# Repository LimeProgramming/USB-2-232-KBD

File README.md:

# USB-2-232-KBD
 Converts USB mice and USB keyboards to serial mice and XT-AT-PS/2 keyboards.

# Development
In progress, not ready for production

## About
This project is an extension of a previous project that you can find here  [previous project that you can find here.](https://github.com/LimeProgramming/USB-serial-mouse-adapter)
My previous project just converted USB mice to Serial mice, this project aims to also convert USB keyboards to XT-AT-PS/2 keyboards. 

# Features
### KVM:
Support for use on KVMs has been added as of version 1.1.1. 
It works fine on my **one**, startech branded, KVM that I have test with. Given that TinyUSB is a bit picky, your results may vary.

## Mouse Features
With this adapter you can convert a modern native USB mouse to a classic serial mouse. 
Want to use an optical mouse on a 386 running Wolfenstein 3D? Well now you can! Want to use a wireless optical mouse on a 486 running Doom? Well you might be able to! (depending on the mouse)

**Supported Protocols:**
- Microsoft Two Button
- Logitech Three Button
- Microsoft Wheel

## Hardware

For the PCB I tried to mimic real keyboard hardware where possible. My old AT keyboard uses 2.2k pull-ups, ferrites, clamp caps and so this PCB does as well for the keyboard interface. Interfacing directly with the GPIO via level shifters uses much higher pullup values, no clamp caps to mitigate signal bounce, no ferrites to mitigate signal noise and importantly, no fuse on the power in line from the host PC. Technically, using a level shifters should work just fine but it is a bit out of spec so early AT and XT machines *may* have issues with level shifters.

I mentioned a fuse, there is a 750ma poly fuse on the PCB as standard. It seems that most AT motherboards have a 1 amp fuse for their keyboard, however that will need to be changed if it pops. While RGB keyboards and mice use more power than the old AT keyboards, there is still more than enough headroom for powering them. Issues can pop up if you're pulling too much power from the keyboard port or back feeding power into the motherboard. For example, my KVM will pull power from the USB port if it is not being powered by it's power adapter, it could potentially pull more than 1 amp, so hopefully the self resetting poly fuse will pop before the 1amp fuse on your motherboard. 

If you want to power the adapter from the keyboard port, put a jumper on pin header J5, label KBDPWR. 
**Important:** If you're powering the adapter using any other methods (eg, built in mini USB, picos micro usb, J4 pin header or a KVM) you must take the jumper off of J5. You risk back feeding a connected computer. 

### Din or PS/2 Port
The PCB can use either a din or a PS/2 port in the same footprint. You can choose which you want to use based on your use case. Recommended use case would be to use the PS/2 port because 6 pin mini din cables are cheap and easy to find.

### Resetting the adapter
Forgot your settings and can't get the adapter working? Don't worry.
There are three different ways to reset the adapter:

#### --- Serial Terminal
As written above, you can reset the adapter back to default settings from the terminal. You can connect to the unused UART of the pico regardless of the settings of the mouse. 

#### --- Small Flat Head Screwdriver

**How To:**
1. Press a small flat head into the position shown above.
2. Power on the adapter and the Picos built-in LED will glow solid.
3. Hold the flat head in position for two or three seconds for the Picos LED to start blinking.
4. Once it is blinking, you can let go of the GPIO and press the reset button.
5. The adapter will boot up with default settings.
#### --- Nuke UF2
**How To:**
1. Download the [flash_nuke.uf2](https://datasheets.raspberrypi.com/soft/flash_nuke.uf2) file.
2. Connect the adapter to your PC using the microusb port built into the Pi Pico.
3. Hold Reset, then bootsel, then release reset then bootsel. This will make the Pico appear as a removable storage device. 
4. Drag the flash_nuke.uf2 file to the storage device. This will reset the flash the on the Pi Pico.
5. The Pico should reboot on its own and show up as a removable storage device again. If it doesn't, tap the reset button.
6. Download the latest firmware and drag that UF2 file to the storage device.
7. The adapter will boot up with default settings.

# Compiling the Firmware
The default mouse settings can be edited in `default_config.h` prior to compilation. You can use this to set the default settings for your own configuration. 

The build environment is a normal PicoSDK setup, there are several guides out the for both Linux and Windows.  From experience the setup is easier in Linux. 

You'll need the following Libs:
 - [**PicoSDK Version: 1.4.0**](https://github.com/raspberrypi/pico-sdk)
 - [**TinyUSB Version: 0.14.0**](https://github.com/hathach/tinyusb)
 - [**TUSB Xinput**](https://github.com/Ryzee119/tusb_xinput)

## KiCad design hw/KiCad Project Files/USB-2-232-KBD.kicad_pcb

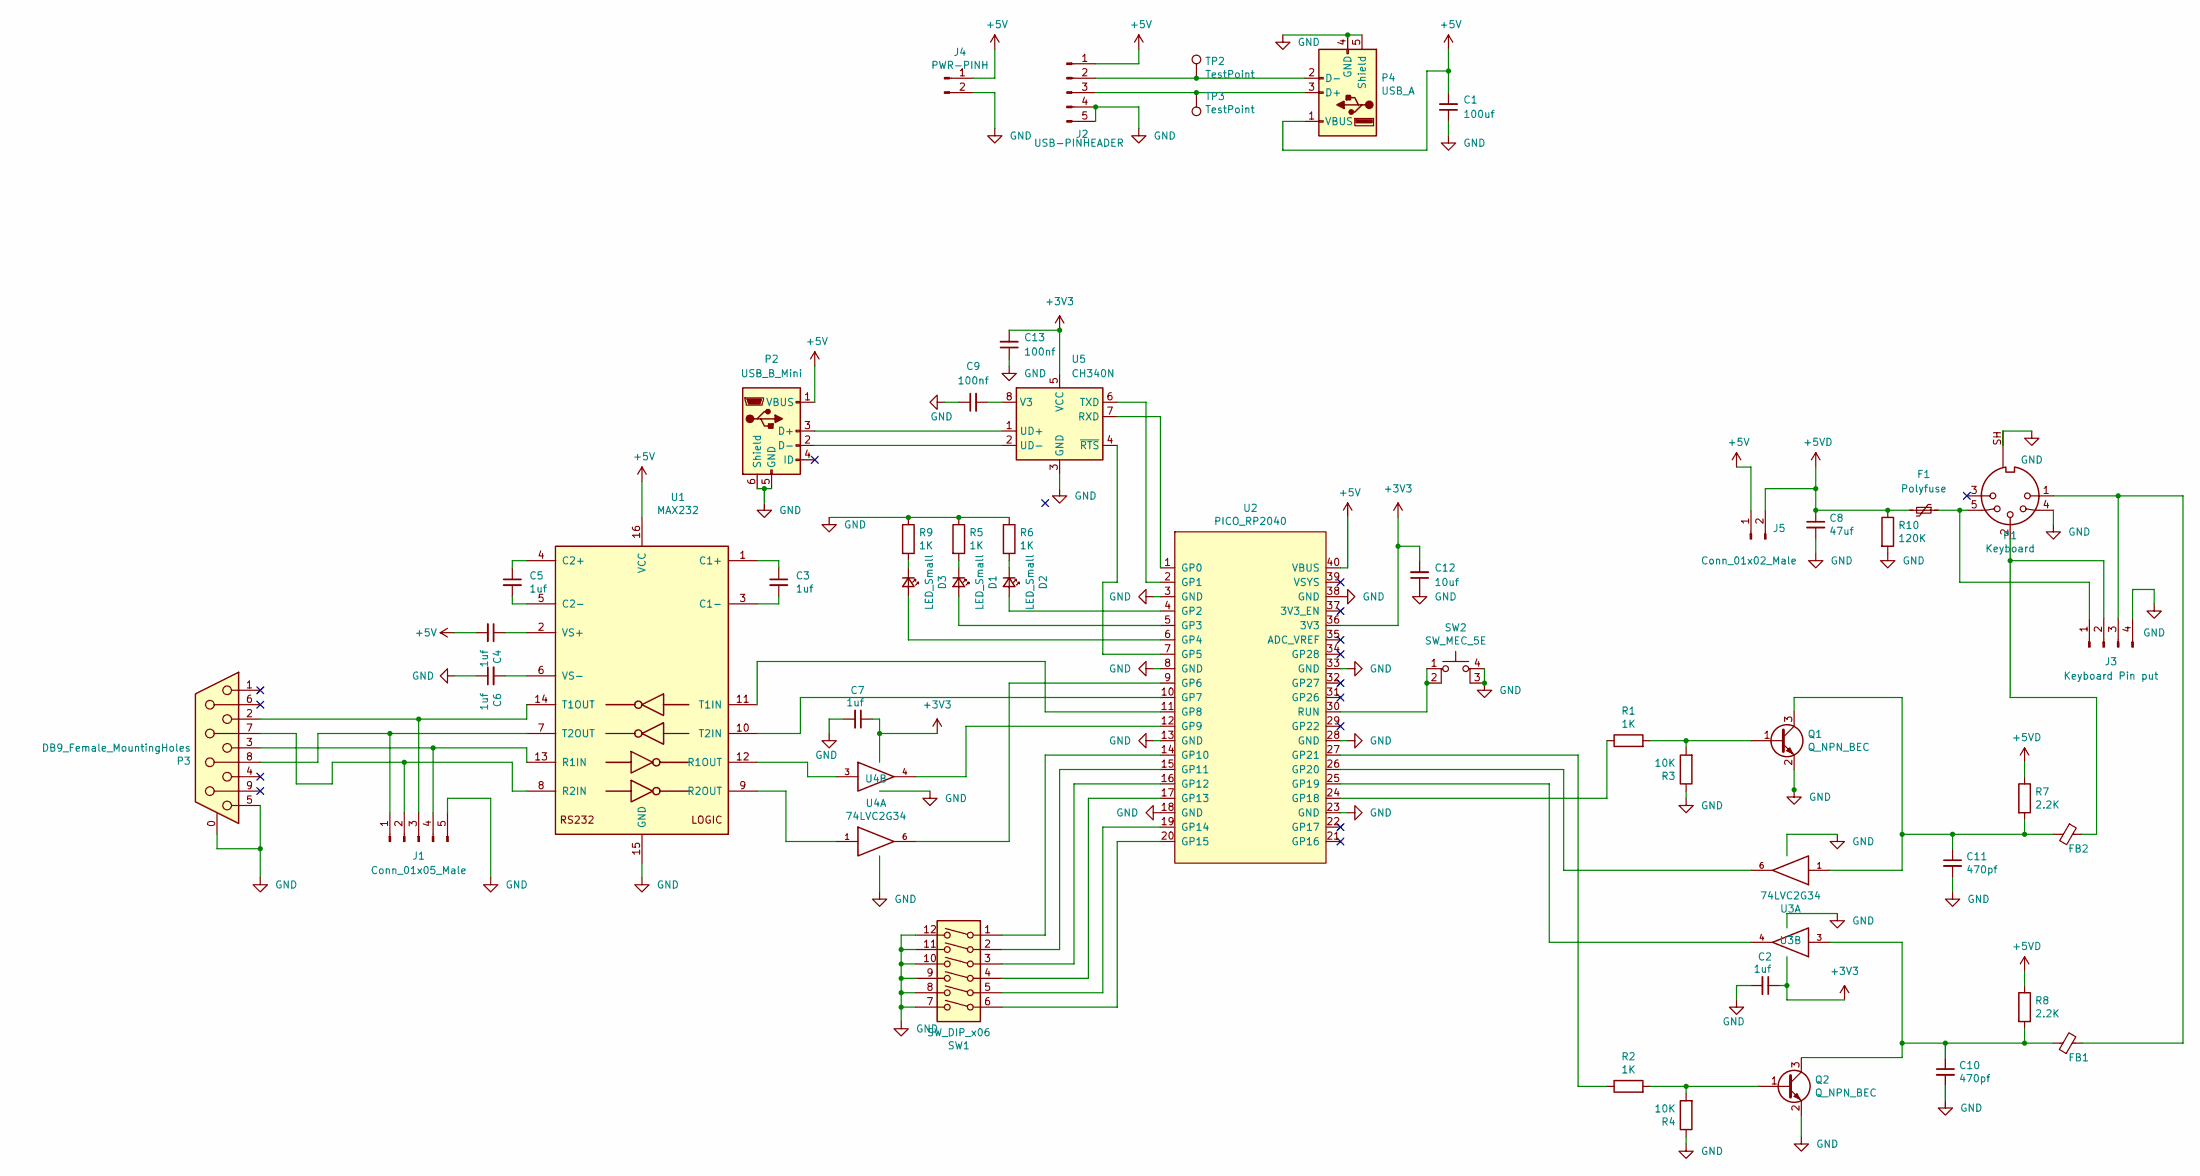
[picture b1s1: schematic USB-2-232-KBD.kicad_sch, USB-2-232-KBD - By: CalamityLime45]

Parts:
C1: 100uf; C_1206_3216Metric; JLC part C15008
C2, C4, C5, C7: 1uf; C_0402_1005Metric; JLC part C52923
C3, C6: 1uf; C_0402_1005Metric_ref-flip; JLC part C52923
C8: 47uf; C_0805_2012Metric; JLC part C16780
C9: 100nf; C_0402_1005Metric; JLC part C1525
C10: 470pf; C_0402_1005Metric
C11: 470pf; C_0402_1005Metric; JLC part C1537
C12: 10uf; C_1206_3216Metric; JLC part C13585
C13: 100nf; C_0402_1005Metric
D1: LED_Small; LED_0805_MOUSE; JLC part C2296
D2: LED_Small; LED_0805_PWR; JLC part C84256
D3: LED_Small; LED_0805_KB; JLC part C2296
F1: Polyfuse; PolyFuse_1206; JLC part C883129
FB1: Ferrite; FB_0805_2012Metric; JLC part C1015
FB2: Ferrite; FB_0805_2012Metric; JLC Part C1015
J1: Conn_01x05_Male; PinHeader_ALT_SERIAL_OUT_V2
J2: USB-PINHEADER; PinHeader_ALT_USB_IN
J3: Keyboard Pin put; AT_Keyboard_pin
J4: PWR-PINH; PinHeader_ALT_PWR_IN
J5: Conn_01x02_Male; PinHeader_PWR_FROM_AT
P1: Keyboard; DIN-PS2-COMBO
P2: USB_B_Mini; USB_Mini-B; JLC part C2977777
P3: DB9_Female_MountingHoles; DSUB-9_Female_Horizontal_P2.77x2.84mm_EdgePinOffset7.70mm_H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
P4: USB_A; USB_A_Wuerth_614004134726_Horizontal
Q1, Q2: Q_NPN_BEC; SOT-23-3; JLC part C8512
R1, R2, R5, R6, R9: 1K; R_0402_LEDS; JLC part C11702
R3, R4: 10K; R_0402_LEDS; JLC part C25744
R7, R8: 2.2K; R_0805_2012Metric; JLC part C17520
R10: 120K; R_0805_2012Metric; JLC Part C17436
SW1: SW_DIP_x06; SW_DIP_SPSTx06_Slide_9.78x17.42mm_W7.62mm_P2.54mm
SW2: SW_MEC_5E; SW_PUSH_6mm
TP2: TestPoint; TP2_Pad_TH_1.5x1.5
TP3: TestPoint; TP3_Pad_TH_1.5x1.5
U1: MAX232; max232_soic-16; JLC part C26860
U2: PICO_RP2040; RPi_Pico_SMD_THv2
U3, U4: 74LVC2G34; SOT-23-6; JLC part C347589
U5: CH340N; JLC part C2977777

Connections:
+3V3: C2.1, C7.1, C12.2, C13.2, U2.36 (3V3), U3.5, U4.5, U5.5 (VCC)
+5V: C1.2, C4.2, J2.1, J4.1, J5.1, P2.1 (VBUS), P4.1 (VBUS), U1.16 (VCC), U2.40 (VBUS)
+5VD: C8.1, F1.2, J5.2, R7.1, R8.1, R10.1
GND: C1.1, C2.2, C6.1, C7.2, C8.2, C9.1, C10.2, C11.2, C12.1, C13.1, J1.5, J2.4, J2.5, J3.4, J4.2, P1.4, P1.SH, P2.5 (GND), P2.6 (Shield), P3.0 (PAD), P3.5, P4.4 (GND), P4.5 (Shield), Q1.2 (E), Q2.2 (E), R3.1, R4.1, R5.1, R6.1, R9.1, R10.2, SW1.7, SW1.8, SW1.9, SW1.10, SW1.11, SW1.12, SW2.3 (K), SW2.4 (A), U1.15 (GND), U2.3 (GND), U2.8 (GND), U2.13 (GND), U2.18 (GND), U2.23 (GND), U2.28 (GND), U2.33 (GND), U2.38 (GND), U3.2, U4.2, U5.3 (GND)
unnamed: C3.1, U1.1 (C1+)
unnamed: C3.2, U1.3 (C1-)
unnamed: C4.1, U1.2 (VS+)
unnamed: C5.1, U1.4 (C2+)
unnamed: C5.2, U1.5 (C2-)
unnamed: C6.2, U1.6 (VS-)
unnamed: C9.2, U5.8 (V3)
unnamed: C10.1, FB1.1, Q2.3 (C), R8.2, U3.3
unnamed: C11.1, FB2.2, Q1.3 (C), R7.2, U3.1
unnamed: D1.1 (K), R5.2
unnamed: D1.2 (A), U2.5 (GP3)
unnamed: D2.1 (K), R6.2
unnamed: D2.2 (A), U2.4 (GP2)
unnamed: D3.1 (K), R9.2
unnamed: D3.2 (A), U2.6 (GP4)
unnamed: F1.1, J3.1, P1.5
unnamed: FB1.2, J3.3, P1.1
unnamed: FB2.1, J3.2, P1.2
unnamed: J1.1, P3.8, U1.7 (T2OUT)
unnamed: J1.2, P3.7, U1.8 (R2IN)
unnamed: J1.3, P3.2, U1.14 (T1OUT)
unnamed: J1.4, P3.3, U1.13 (R1IN)
unnamed: J2.2, P4.2 (D-), TP2.1
unnamed: J2.3, P4.3 (D+), TP3.1
unnamed: P2.2 (D-), U5.2 (UD-)
unnamed: P2.3 (D+), U5.1 (UD+)
unnamed: Q1.1 (B), R1.2, R3.2
unnamed: Q2.1 (B), R2.2, R4.2
unnamed: R1.1, U2.24 (GP18)
unnamed: R2.1, U2.27 (GP21)
unnamed: SW1.1, U2.14 (GP10)
unnamed: SW1.2, U2.15 (GP11)
unnamed: SW1.3, U2.16 (GP12)
unnamed: SW1.4, U2.17 (GP13)
unnamed: SW1.5, U2.19 (GP14)
unnamed: SW1.6, U2.20 (GP15)
unnamed: SW2.1, SW2.2, U2.30 (RUN)
unnamed: U1.9 (R2OUT), U4.1
unnamed: U1.10 (T2IN), U2.10 (GP7)
unnamed: U1.11 (T1IN), U2.11 (GP8)
unnamed: U1.12 (R1OUT), U4.3
unnamed: U2.1 (GP0), U5.7 (RXD)
unnamed: U2.2 (GP1), U5.6 (TXD)
unnamed: U2.7 (GP5), U5.4 (~RTS)
unnamed: U2.9 (GP6), U4.6
unnamed: U2.12 (GP9), U4.4
unnamed: U2.25 (GP19), U3.4
unnamed: U2.26 (GP20), U3.6

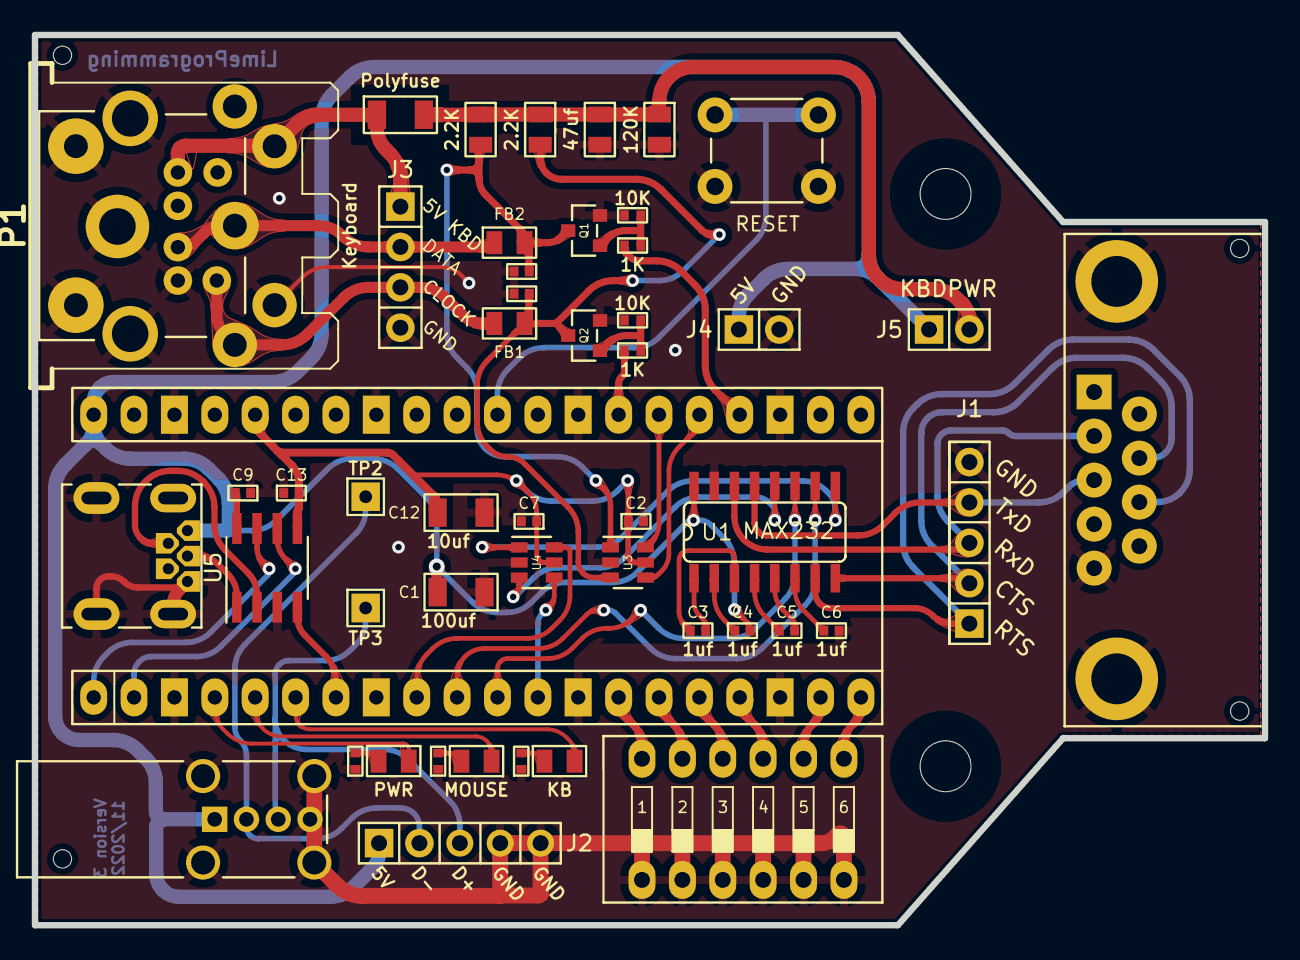
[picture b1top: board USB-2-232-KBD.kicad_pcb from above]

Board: 2 copper layers, 77.4 x 56.0 mm, 49 parts (0 on the bottom side), 52 nets.

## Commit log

2022-11-07 init upload
2022-11-07 Add gerber files
2022-11-07 images
2022-11-07 readme
2022-11-07 init firmware upload
2022-11-07 Adding support for set 3
2022-11-07 implementing stored keyboard settings
2022-11-08 WIP ps/2 command set
2022-11-08 improved XT support
2022-11-08 initial implementation of typematic
2022-11-19 fixing up the idle locks
2022-11-19 idle lock leds works a little better now
2022-11-20 Hardware update
    Added a Bleed resistor. My AT machine has a bleed resistor of 150R, so I added a bleed resistor of 120K to the PCB. It shouldn't interfere with the keyboard controller nor add much to power draw but 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
2022-11-20 fixed JLCPCB gerber
2022-11-26 Create Drivers
2022-11-26 Custom Mouse Drivers
    CT mouse v2.0A
2022-11-26 Custom mouse drivers
    CT mouse V2.1b
2022-11-26 Modified Mouse Drivers
    Cutemouse version 1.9.1
2022-12-03 Scrap of planned feature
    Originally I planned to allow the user to set bios overwrites for the keyboard locks, I couldn't implement it in a way I liked that that also didn't look really weird to an end user. So better to scr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
2022-12-11 bug fix
    it now lets go of buttons properly
2022-12-19 update to xbox controller
2023-01-07 update
    Any keys held by a keyboard are depressed if the USB keyboard is unplugged
2023-01-08 updte
    missed this file
2023-01-09 Update
    some cleaning
2023-01-09 Update
    update
2024-07-07 small update
2024-07-09 update
    seems like the update to tinyusb is promising. now if I still had my old microsoft keyboard with tons of consumer keyboard buttons, it might be fun
